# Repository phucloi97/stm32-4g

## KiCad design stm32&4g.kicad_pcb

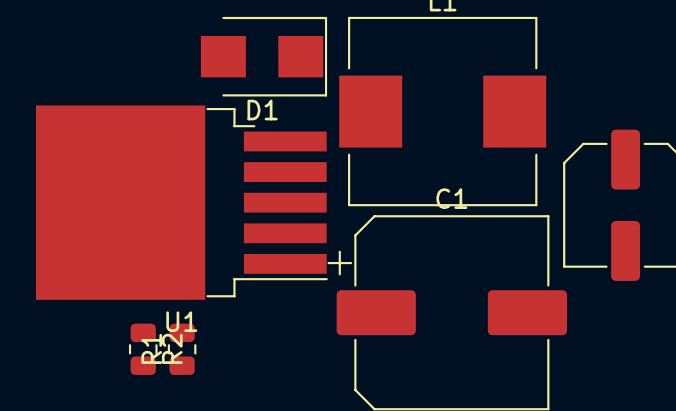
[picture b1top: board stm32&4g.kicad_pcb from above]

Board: 2 copper layers, 7 parts (0 on the bottom side), 5 nets, no tracks yet.

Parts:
C1: 470uF; CP_Elec_10x10.5
C2: 330uF; C_Elec_6.3x7.7
D1: 40v; D_SMB
L1: 33uH - 3.5A; L_Wuerth_HCI-1040
R1: 1k; R_0805_2012Metric
R2: 2.2k; R_0805_2012Metric
U1: LM2596S-ADJ; TO-263-5_TabPin3

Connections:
+4V: C2.1, L1.2, R2.2
GND: C1.2, C2.2, D1.2 (A), R1.1, U1.3 (GND), U1.5 (~ON/OFF)
unnamed: D1.1 (K), L1.1, U1.2 (OUT)
unnamed: R1.2, R2.1, U1.4 (FB)
VCC: C1.1, U1.1 (VIN)

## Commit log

2022-02-20 init project
